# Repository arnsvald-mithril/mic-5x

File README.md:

# MIC-5X — Indoor Microclimate Monitor

**MITHRIL ELECTRONICS** · Doc. MTH-DS-0001 · Datasheet Rev. C.1

A 5-parameter indoor microclimate monitor built on a bare ESP8266 (ESP-12F)
module with a custom-designed analog dust-sensing front-end — not a
pre-built sensor module, but a discrete nephelometric channel (IR LED +
photodiode + LM358 transimpedance amplifier) designed, simulated, and
laid out from scratch.

*(replace with actual board photo/render)*

## Measured parameters

| Parameter          | Sensor  | Interface |
|---------------------|---------|-----------|
| Temperature          | DHT22   | Digital (1-Wire-like) |
| Relative humidity     | DHT22   | Digital |
| Barometric pressure    | BMP280  | I2C |
| Illuminance          | BH1750  | I2C |
| Particulate matter (dust) | Custom analog nephelometric channel | ADC (ESP8266 TOUT) |

Full electrical characteristics, error budget, and mechanical drawings:
see `datasheet/MIC-5X_Datasheet_RevC1.pdf`.

## Engineering highlights

- **Analog front-end design.** Custom TIA stage (LM358) for the dust
  channel, simulated in LTspice: DC transfer characteristic
  0.3-3.3 V at 0-30 uA photocurrent, two-pole filter (tau ~= 1.8 ms,
  -3 dB at ~90 Hz). See `hardware/simulation/`.
- **Full error budget.** Aggregated RSS error ~5-7%, dominated by LED
  thermal drift (~4-6%), with contributions from Vref/AMS1117 (~1.5%),
  R3 tempco (~0.3%), and LM358 bias current (~0.5%).
- **Bare-module hardware design.** Migrated from a NodeMCU dev board
  to a bare ESP-12F module with full boot-strapping (EN/RST/GPIO0/GPIO2
  pull-ups, GPIO15 pull-down), a complete power protection chain
  (PolyFuse -> Schottky -> TVS -> AMS1117), and ADC input protection
  for the dust channel.
- **DRC-clean 2-layer PCB** in KiCad, including ground pour with
  stitching vias.
- **Non-blocking firmware.** ~300-line Arduino sketch using millis()
  scheduling (no delay()), with sensor cross-validation (DHT22 vs
  BMP280 temperature check), pressure trend detection, and a fallback
  AP mode for field configuration.
- **3D-printed enclosure**, parametrically modeled in CadQuery, with
  snap-fit assembly (no screws) and a dedicated cross-flow air path
  for the dust sensor.

## Repository structure

```
mic-5x/
    hardware/
        schematic/     KiCad schematic + PDF export
        pcb/            KiCad PCB layout
        simulation/     LTspice results (TIA transfer & frequency response)
    firmware/           ESP8266 Arduino firmware
    enclosure/           CadQuery enclosure script + STEP/STL exports
    datasheet/           Full Rev. C.1 datasheet (PDF)
    docs/images/         Board photos, renders, simulation plots
```

## Known limitations

This is an honest engineering datasheet, not a marketing sheet —
current known issues:

- Dust channel is **not yet calibrated on real aerosol**; the
  0.3-3.3 V range is the simulated full-scale transfer characteristic,
  not a validated ppm/ug*m^-3 curve.
- Enclosure snap-fit tongues are sized for **PLA** specifically
  (~0.9% strain after redesign); other materials would need
  re-verification of engagement geometry.
- LTspice .asc source files were iterated in a single working draft
  and not preserved as separate versions — simulation plots are
  archived in docs/images/, and the circuit is fully reproducible
  from the parameters listed in the datasheet.
- Enclosure errata (S6.6 of the datasheet) documents six issues found
  during design review and their fixes (exhaust port, fan bore
  clearance, snap-fit strain, screw sizing, stray light path).

## License

MIT — see LICENSE.

## Author

Oleksandr Didyk — Bachelor of Electronics, Igor Sikorsky Kyiv
Polytechnic Institute, Faculty of Electronics, specialization in
Electronic Devices and Systems.

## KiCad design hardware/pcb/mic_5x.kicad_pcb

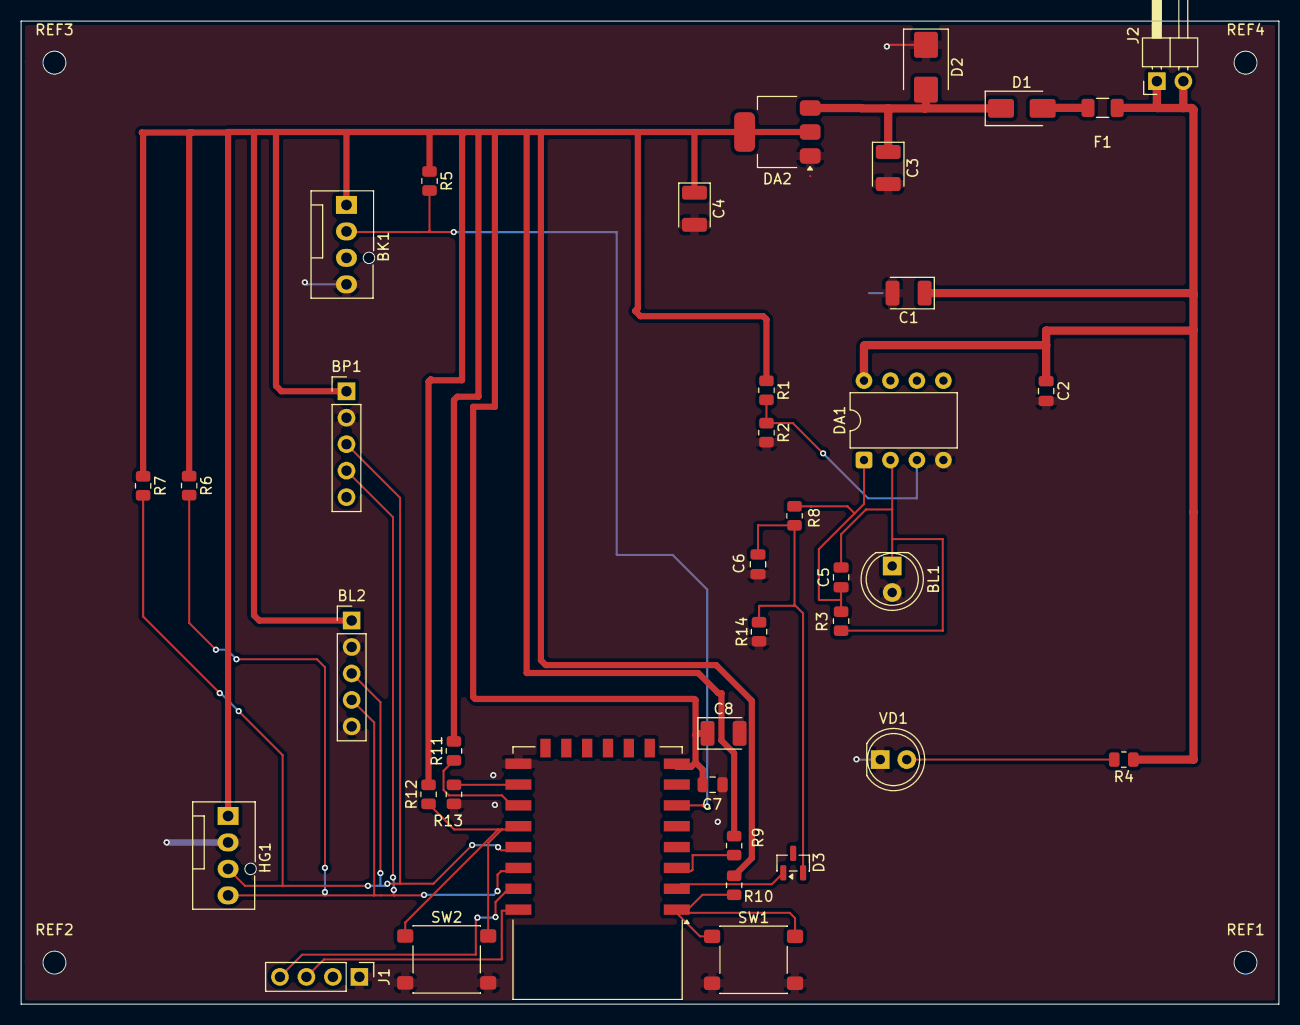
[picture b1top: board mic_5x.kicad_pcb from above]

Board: 2 copper layers, 120.7 x 94.3 mm, 43 parts (0 on the bottom side), 21 nets.

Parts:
BK1: DHT22; FanPinHeader_1x04_P2.54mm_Vertical
BL1: D_Photo; LED_D5.0mm
BL2: BH1750; PinHeader_1x05_P2.54mm_Vertical
BP1: BMP280; PinHeader_1x05_P2.54mm_Vertical
C1, C8: 10u; CP_EIA-3528-21_Kemet-B
C2, C7: 100n; C_0805_2012Metric
C3, C4: 22u; CP_EIA-3528-21_Kemet-B
C5: 10n; C_0805_2012Metric
C6: 1u; C_0805_2012Metric
D1: D_Schottky; D_SMA
D2: D_TVS; D_SMB
D3: D_Schottky; SOT-23
DA1: LM358_DFN; DIP-8_W7.62mm
DA2: AMS1117-3.3; SOT-223-3_TabPin2
DD1: ESP-12E
F1: Polyfuse; Fuse_1206_3216Metric
HG1: OLED; FanPinHeader_1x04_P2.54mm_Vertical
J1: Conn_01x04; PinHeader_1x04_P2.54mm_Vertical
J2: Conn_01x02; PinHeader_1x02_P2.54mm_Horizontal
R1, R5, R9, R10, R11, R12, R13: 10k; R_0805_2012Metric
R2: 1k; R_0805_2012Metric
R3: 100k; R_0805_2012Metric
R4: 68; R_0805_2012Metric
R6, R7: 4k7; R_0805_2012Metric
R8: 4,7k; R_0805_2012Metric
R14: 1.8k; R_0805_2012Metric
REF1, REF2, REF3, REF4: MountingHole_2.2mm_M2
SW1, SW2: SW_SPST; SW_SPST_PTS645Sx43SMTR92
VD1: LED; LED_D5.0mm

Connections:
+3V: BK1.1, BL2.1, BP1.1, C4.1, C7.1, C8.1, DA2.2 (VO), DD1.8 (VCC), HG1.1, R1.1, R5.1, R6.1, R7.1, R9.2, R10.2, R11.2, R12.2
+5V: C1.1, C2.1, DA1.8 (V+), F1.1, J2.1, J2.2, R4.1
GND: BK1.4, BL1.2 (A), BL2.2, BL2.5, BP1.2, C1.2, C2.2, C3.2, C4.2, C6.2, C7.2, C8.2, D2.1 (A1), DA1.4 (V-), DA2.1 (GND), DD1.15 (GND), HG1.2, J1.1, R2.2, R13.1, R14.1, SW1.2 (B), SW2.2 (B), VD1.1 (K)
unnamed: BK1.2, DD1.6 (GPIO12), R5.2
unnamed: BL1.1 (K), C5.2, DA1.2 (-), R3.2
unnamed: BL2.3, BP1.3, DD1.19 (GPIO4), HG1.3, R7.2
unnamed: BL2.4, BP1.4, DD1.20 (GPIO5), HG1.4, R6.2
unnamed: C5.1, DA1.1, R3.1, R8.1
unnamed: D1.2 (A), F1.2
unnamed: C3.1, D1.1 (K), D2.2 (A2), DA2.3 (VI)
unnamed: C6.1, D3.2 (A), R8.2, R14.2
unnamed: D3.1 (K), DD1.2 (ADC)
unnamed: DA1.3 (+), R1.2, R2.1
unnamed: DD1.3 (EN), R9.1
unnamed: DD1.18 (GPIO0), R12.1, SW2.1 (A)
unnamed: DD1.22 (GPIO1/TXD), J1.3
unnamed: DD1.17 (GPIO2), R11.1
unnamed: DD1.21 (GPIO3/RXD), J1.4
unnamed: DD1.16 (GPIO15), R13.2
unnamed: DD1.1 (~RST), R10.1, SW1.1 (A)
unnamed: R4.2, VD1.2 (A)
